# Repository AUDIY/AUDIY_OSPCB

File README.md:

# AUDIY_OSPCB
Open Source PCB Files Engineered by AUDIY

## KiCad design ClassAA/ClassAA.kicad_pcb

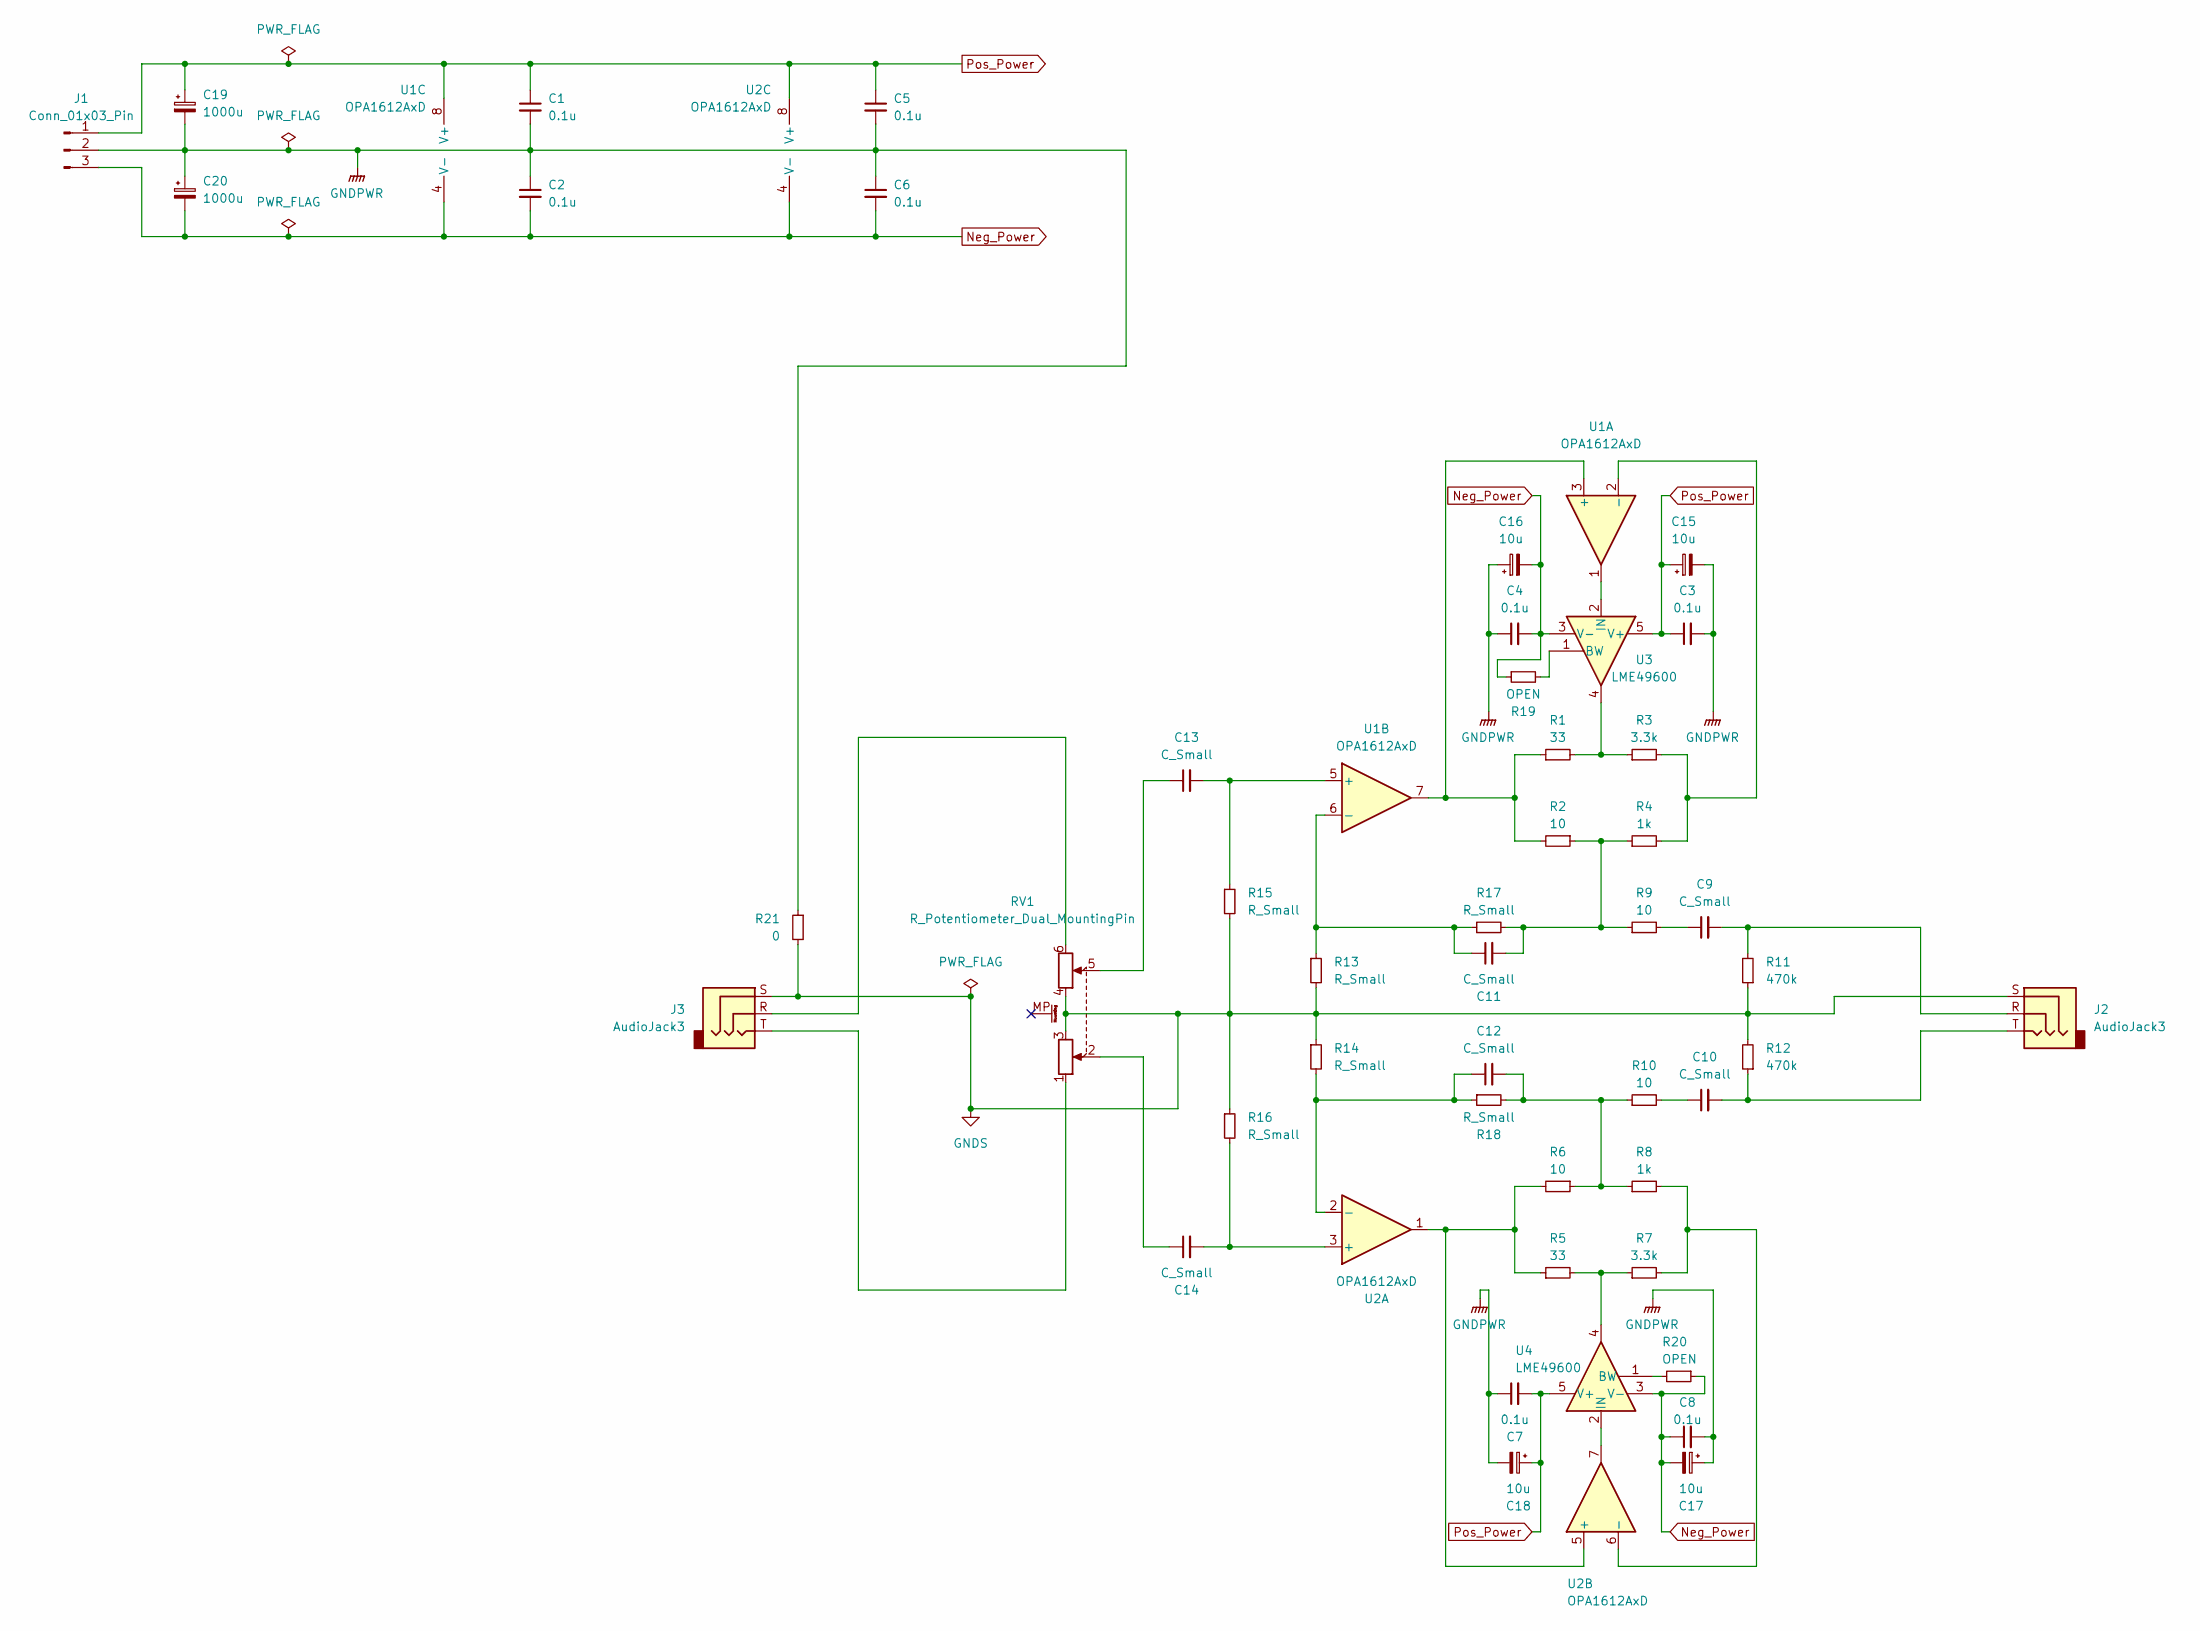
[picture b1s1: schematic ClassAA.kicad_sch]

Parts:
C1, C2, C3, C4, C5, C6, C7, C8: 0.1u; C_1206_3216Metric_Pad1.33x1.80mm_HandSolder
C9, C10, C11, C12, C13, C14: C_Small; C_1206_3216Metric_Pad1.33x1.80mm_HandSolder
C15, C16, C17, C18: 10u; CP_Elec_5x5.9
C19, C20: 1000u; CP_Radial_D16.0mm_P7.50mm
J1: Conn_01x03_Pin; JST_VH_B3P-VH_1x03_P3.96mm_Vertical
J2, J3: AudioJack3; Jack_3.5mm_CUI_SJ1-3523N_Horizontal
R1, R5: 33; R_MELF_MMB-0207
R2, R6, R9, R10: 10; R_MELF_MMB-0207
R3, R7: 3.3k; R_MELF_MMB-0207
R4, R8: 1k; R_MELF_MMB-0207
R11, R12: 470k; R_MELF_MMB-0207
R13, R14, R15, R16, R17, R18: R_Small; R_MELF_MMB-0207
R19, R20: OPEN; R_MELF_MMB-0207
R21: 0; R_MELF_MMB-0207
RV1: R_Potentiometer_Dual_MountingPin; Potentiometer_Alps_RK09L_Double_Horizontal
U1, U2: OPA1612AxD; SOIC-8_3.9x4.9mm_P1.27mm
U3, U4: LME49600; TO-263-5_TabPin3

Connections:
GNDPWR: C1.2, C2.1, C3.2, C4.1, C5.2, C6.1, C7.1, C8.2, C15.2, C16.1, C17.1, C18.2, C19.2, C20.1, J1.2, R21.1
GNDS: J2.S, J3.S, R11.1, R12.2, R13.2, R14.1, R15.2, R16.1, R21.2, RV1.3, RV1.4
Neg_Power: C2.2, C4.2, C6.2, C8.1, C16.2, C17.2, C20.2, J1.3, R19.1, R20.1, U1.4 (V-), U2.4 (V-), U3.3 (V-), U4.3 (V-)
unnamed: C9.1, R9.2
unnamed: C9.2, J2.R, R11.2
unnamed: C10.1, R10.2
unnamed: C10.2, J2.T, R12.1
unnamed: C11.2, R2.1, R4.1, R9.1, R17.2
unnamed: C12.2, R6.1, R8.1, R10.1, R18.2
unnamed: C13.1, RV1.5
unnamed: C14.1, RV1.2
unnamed: J3.R, RV1.6
unnamed: J3.T, RV1.1
unnamed: R1.2, R3.1, U3.4
unnamed: R5.2, R7.1, U4.4
unnamed: R1.1, R2.2, U1.3 (+), U1.7
unnamed: R3.2, R4.2, U1.2 (-)
unnamed: C13.2, R15.1, U1.5 (+)
unnamed: C11.1, R13.1, R17.1, U1.6 (-)
unnamed: C14.2, R16.2, U2.3 (+)
unnamed: C12.1, R14.2, R18.1, U2.2 (-)
unnamed: R5.1, R6.2, U2.1, U2.5 (+)
unnamed: R7.2, R8.2, U2.6 (-)
unnamed: R19.2, U3.1 (BW)
unnamed: U1.1, U3.2 (IN)
unnamed: R20.2, U4.1 (BW)
unnamed: U2.7, U4.2 (IN)
Pos_Power: C1.1, C3.1, C5.1, C7.2, C15.1, C18.1, C19.1, J1.1, U1.8 (V+), U2.8 (V+), U3.5 (V+), U4.5 (V+)

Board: 2 copper layers, 49 parts (0 on the bottom side), 28 nets, no tracks yet.

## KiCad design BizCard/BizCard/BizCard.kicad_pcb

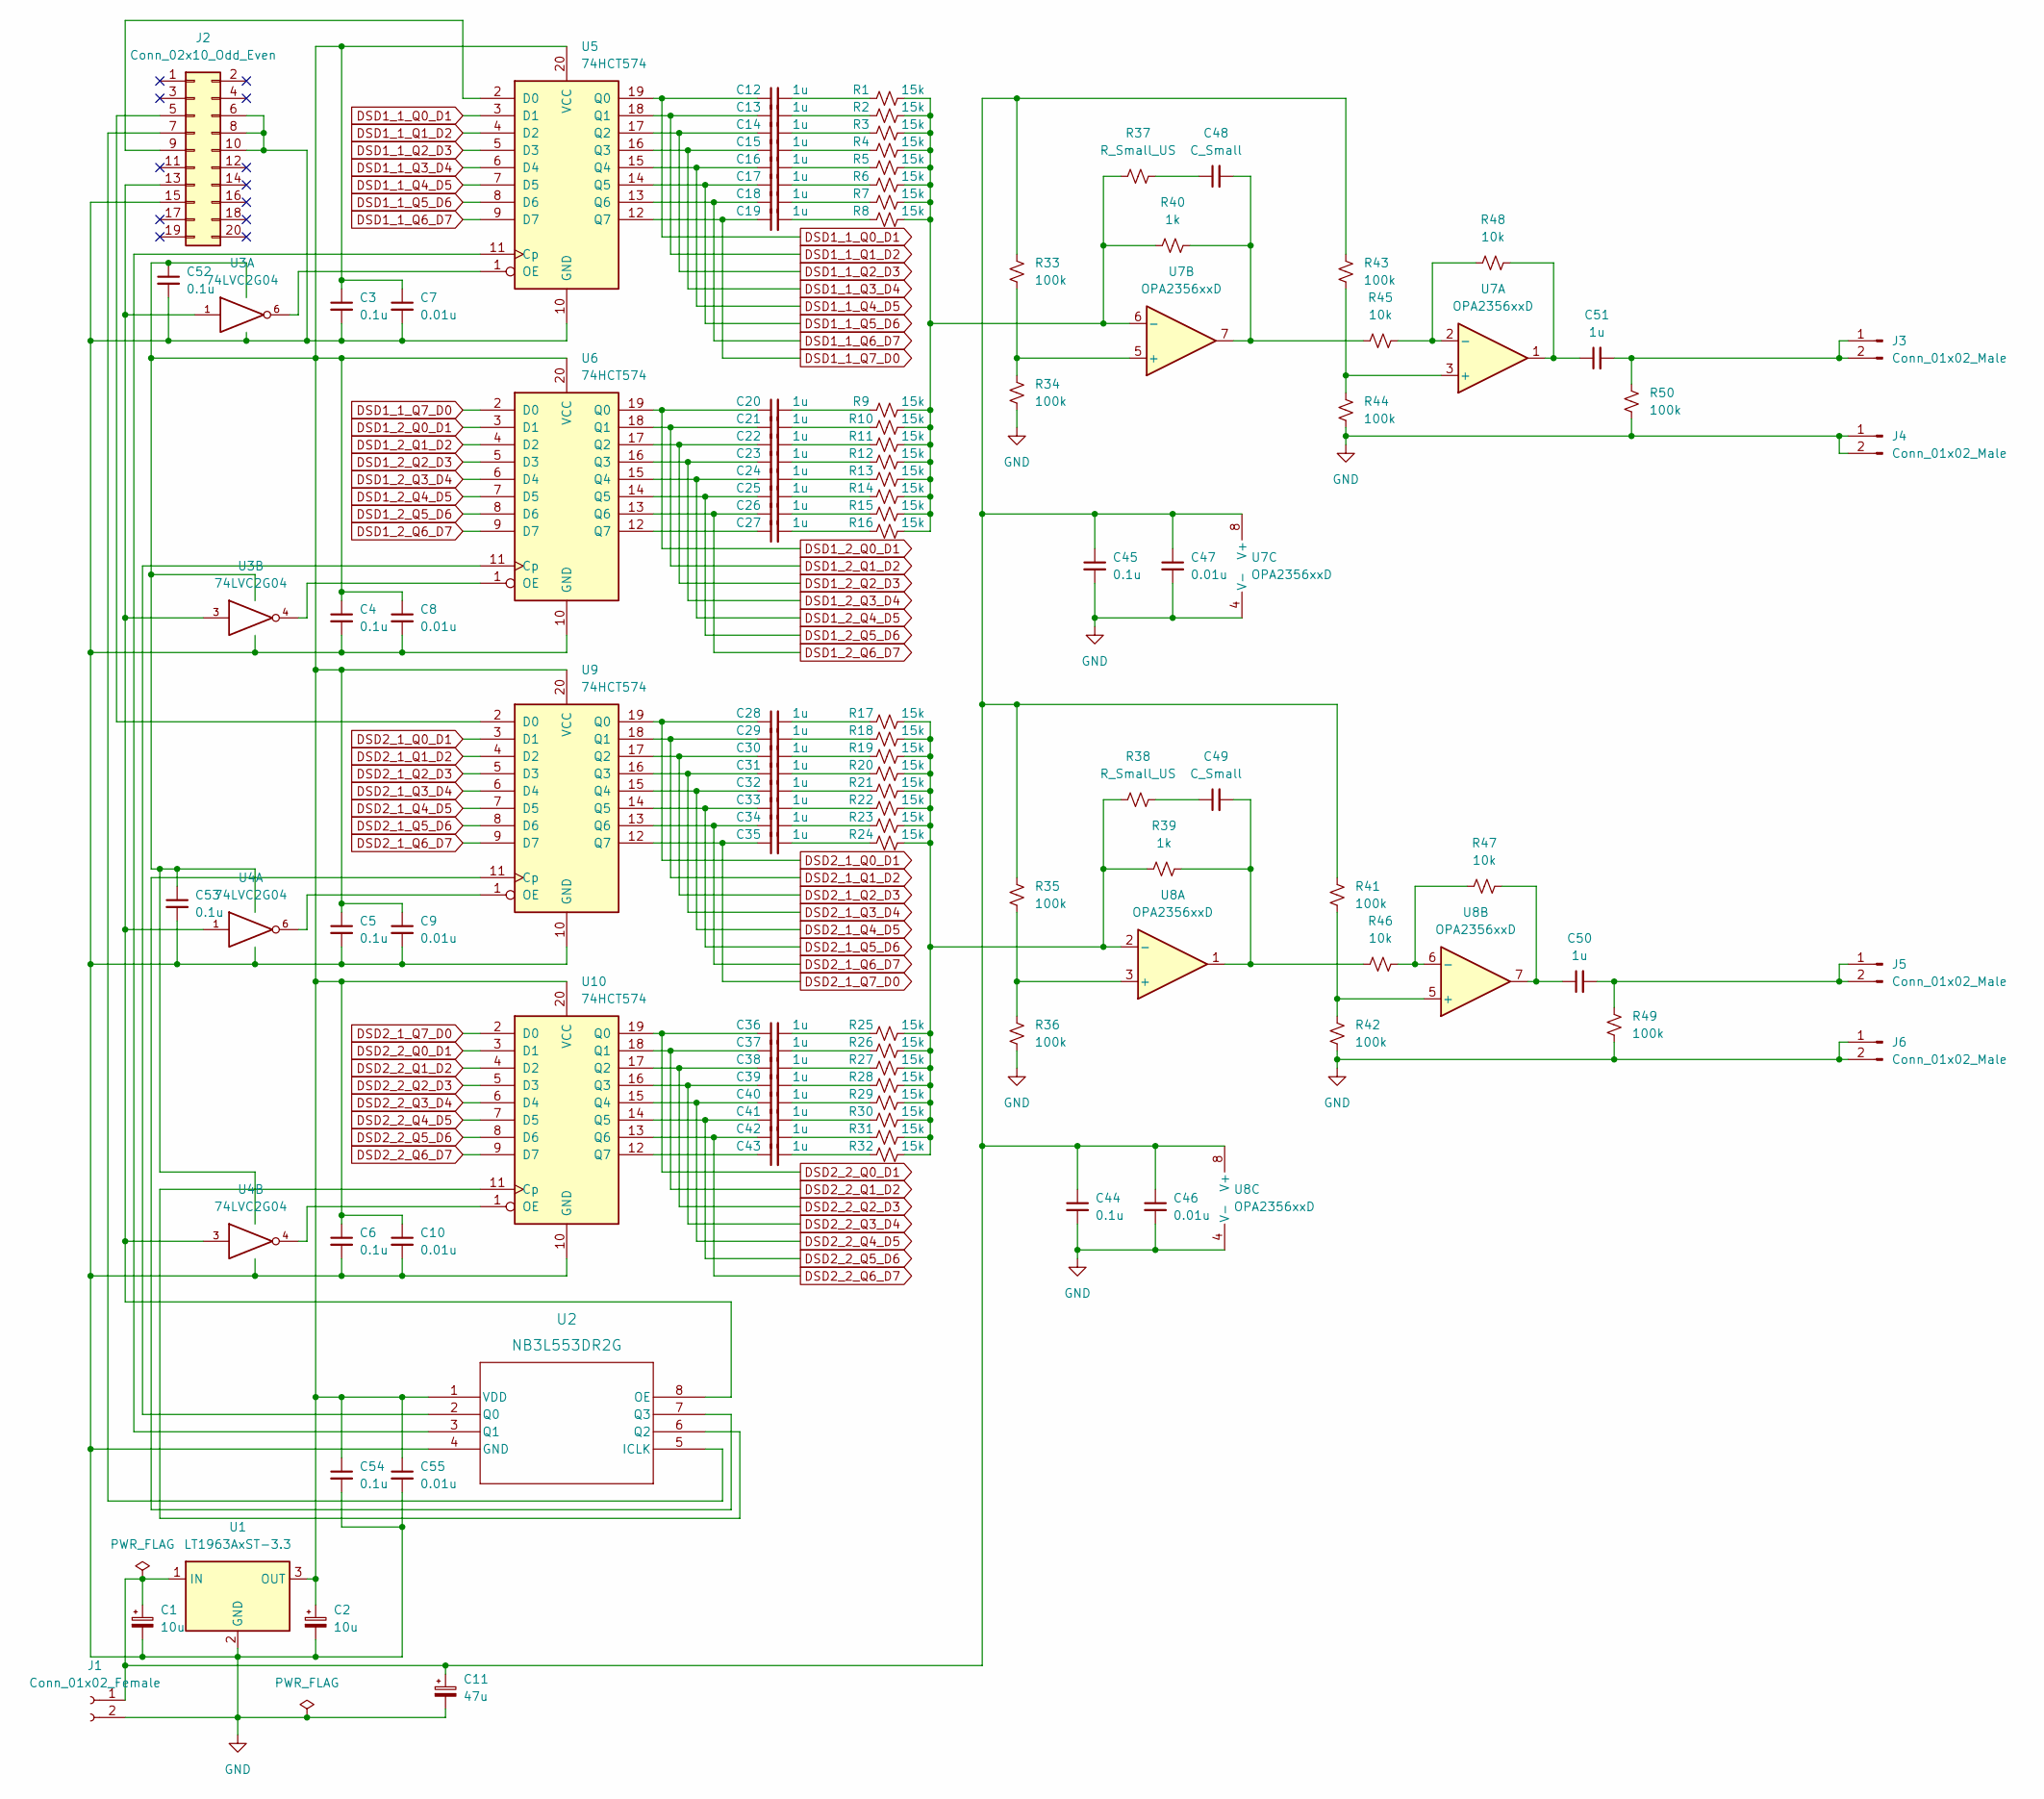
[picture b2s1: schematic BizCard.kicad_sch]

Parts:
C1, C2: 10u; CP_Elec_4x5.4
C3, C4, C5, C6, C44, C45, C52, C53, C54: 0.1u; C_0603_1608Metric_Pad1.08x0.95mm_HandSolder
C7, C8, C9, C10, C46, C47, C55: 0.01u; C_0603_1608Metric_Pad1.08x0.95mm_HandSolder
C11: 47u; CP_Elec_5x5.9
C12, C13, C14, C15, C16, C17, C18, C19, C20, C21, C22, C23, C24, C25, C26, C27, C28, C29, C30, C31, C32, C33, C34, C35, C36, C37, C38, C39, C40, C41, C42, C43, C50, C51: 1u; C_0603_1608Metric_Pad1.08x0.95mm_HandSolder
C48, C49: C_Small; C_0603_1608Metric_Pad1.08x0.95mm_HandSolder
J1: Conn_01x02_Female; JST_PH_B2B-PH-K_1x02_P2.00mm_Vertical
J2: Conn_02x10_Odd_Even; PinHeader_2x10_P2.54mm_Vertical
J3, J4, J5, J6: Conn_01x02_Male; PinHeader_1x02_P2.54mm_Vertical
R1, R2, R3, R4, R5, R6, R7, R8, R9, R10, R11, R12, R13, R14, R15, R16, R17, R18, R19, R20, R21, R22, R23, R24, R25, R26, R27, R28, R29, R30, R31, R32: 15k; R_0603_1608Metric_Pad0.98x0.95mm_HandSolder
R33, R34, R35, R36, R41, R42, R43, R44, R49, R50: 100k; R_0603_1608Metric_Pad0.98x0.95mm_HandSolder
R37, R38: R_Small_US; R_0603_1608Metric_Pad0.98x0.95mm_HandSolder
R39, R40: 1k; R_0603_1608Metric_Pad0.98x0.95mm_HandSolder
R45, R46, R47, R48: 10k; R_0603_1608Metric_Pad0.98x0.95mm_HandSolder
U1: LT1963AxST-3.3; SOT-223-3_TabPin2
U2: NB3L553DR2G; SOIC8_ONS
U3, U4: 74LVC2G04; SOT-363_SC-70-6_Handsoldering
U5, U6, U9, U10: 74HCT574; SOIC-20W_7.5x12.8mm_P1.27mm
U7, U8: OPA2356xxD; SOIC-8_3.9x4.9mm_P1.27mm

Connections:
DSD1_1_Q0_D1: C12.1, U5.3 (D1), U5.19 (Q0)
DSD1_1_Q1_D2: C13.1, U5.4 (D2), U5.18 (Q1)
DSD1_1_Q2_D3: C14.1, U5.5 (D3), U5.17 (Q2)
DSD1_1_Q3_D4: C15.1, U5.6 (D4), U5.16 (Q3)
DSD1_1_Q4_D5: C16.1, U5.7 (D5), U5.15 (Q4)
DSD1_1_Q5_D6: C17.1, U5.8 (D6), U5.14 (Q5)
DSD1_1_Q6_D7: C18.1, U5.9 (D7), U5.13 (Q6)
DSD1_1_Q7_D0: C19.1, U5.12 (Q7), U6.2 (D0)
DSD1_2_Q0_D1: C20.1, U6.3 (D1), U6.19 (Q0)
DSD1_2_Q1_D2: C21.1, U6.4 (D2), U6.18 (Q1)
DSD1_2_Q2_D3: C22.1, U6.5 (D3), U6.17 (Q2)
DSD1_2_Q3_D4: C23.1, U6.6 (D4), U6.16 (Q3)
DSD1_2_Q4_D5: C24.1, U6.7 (D5), U6.15 (Q4)
DSD1_2_Q5_D6: C25.1, U6.8 (D6), U6.14 (Q5)
DSD1_2_Q6_D7: C26.1, U6.9 (D7), U6.13 (Q6)
DSD2_1_Q0_D1: C28.1, U9.3 (D1), U9.19 (Q0)
DSD2_1_Q1_D2: C29.1, U9.4 (D2), U9.18 (Q1)
DSD2_1_Q2_D3: C30.1, U9.5 (D3), U9.17 (Q2)
DSD2_1_Q3_D4: C31.1, U9.6 (D4), U9.16 (Q3)
DSD2_1_Q4_D5: C32.1, U9.7 (D5), U9.15 (Q4)
DSD2_1_Q5_D6: C33.1, U9.8 (D6), U9.14 (Q5)
DSD2_1_Q6_D7: C34.1, U9.9 (D7), U9.13 (Q6)
DSD2_1_Q7_D0: C35.1, U9.12 (Q7), U10.2 (D0)
DSD2_2_Q0_D1: C36.1, U10.3 (D1), U10.19 (Q0)
DSD2_2_Q1_D2: C37.1, U10.4 (D2), U10.18 (Q1)
DSD2_2_Q2_D3: C38.1, U10.5 (D3), U10.17 (Q2)
DSD2_2_Q3_D4: C39.1, U10.6 (D4), U10.16 (Q3)
DSD2_2_Q4_D5: C40.1, U10.7 (D5), U10.15 (Q4)
DSD2_2_Q5_D6: C41.1, U10.8 (D6), U10.14 (Q5)
DSD2_2_Q6_D7: C42.1, U10.9 (D7), U10.13 (Q6)
GND: C1.2, C2.2, C3.2, C4.2, C5.2, C6.2, C7.2, C8.2, C9.2, C10.2, C11.2, C44.2, C45.2, C46.2, C47.2, C52.2, C53.2, C54.2, C55.2, J1.2, J2.6, J2.8, J2.10, J2.15, J4.1, J4.2, J6.1, J6.2, R34.2, R36.2, R42.2, R44.2, R49.2, R50.2, U1.2 (GND), U2.4 (GND), U3.2 (GND), U4.2 (GND), U5.10 (GND), U6.10 (GND), U7.4 (V-), U8.4 (V-), U9.10 (GND), U10.10 (GND)
unnamed: C1.1, C11.1, C44.1, C45.1, C46.1, C47.1, J1.1, R33.1, R35.1, R41.1, R43.1, U1.1 (IN), U7.8 (V+), U8.8 (V+)
unnamed: C12.2, R1.1
unnamed: C13.2, R2.1
unnamed: C14.2, R3.1
unnamed: C15.2, R4.1
unnamed: C16.2, R5.1
unnamed: C17.2, R6.1
unnamed: C18.2, R7.1
unnamed: C19.2, R8.1
unnamed: C20.2, R9.1
unnamed: C21.2, R10.1
unnamed: C22.2, R11.1
unnamed: C23.2, R12.1
unnamed: C24.2, R13.1
unnamed: C25.2, R14.1
unnamed: C26.2, R15.1
unnamed: C27.1, U6.12 (Q7)
unnamed: C27.2, R16.1
unnamed: C28.2, R17.1
unnamed: C29.2, R18.1
unnamed: C30.2, R19.1
unnamed: C31.2, R20.1
unnamed: C32.2, R21.1
unnamed: C33.2, R22.1
unnamed: C34.2, R23.1
unnamed: C35.2, R24.1
unnamed: C36.2, R25.1
unnamed: C37.2, R26.1
unnamed: C38.2, R27.1
unnamed: C39.2, R28.1
unnamed: C40.2, R29.1
unnamed: C41.2, R30.1
unnamed: C42.2, R31.1
unnamed: C43.1, U10.12 (Q7)
unnamed: C43.2, R32.1
unnamed: C48.1, R37.2
unnamed: C48.2, R40.1, R45.1, U7.7
unnamed: C49.1, R38.2
unnamed: C49.2, R39.1, R46.1, U8.1
unnamed: C50.1, R47.2, U8.7
unnamed: C50.2, J5.1, J5.2, R49.1
unnamed: C51.1, R48.2, U7.1
unnamed: C51.2, J3.1, J3.2, R50.1
unnamed: J2.7, U2.5 (ICLK)
unnamed: J2.13, U2.8 (OE), U3.1, U3.3, U4.1, U4.3
unnamed: R1.2, R2.2, R3.2, R4.2, R5.2, R6.2, R7.2, R8.2, R9.2, R10.2, R11.2, R12.2, R13.2, R14.2, R15.2, R16.2, R37.1, R40.2, U7.6 (-)
unnamed: R17.2, R18.2, R19.2, R20.2, R21.2, R22.2, R23.2, R24.2, R25.2, R26.2, R27.2, R28.2, R29.2, R30.2, R31.2, R32.2, R38.1, R39.2, U8.2 (-)
unnamed: R35.2, R36.1, U8.3 (+)
unnamed: R41.2, R42.1, U8.5 (+)
unnamed: R43.2, R44.1, U7.3 (+)
unnamed: R45.2, R48.1, U7.2 (-)
unnamed: R46.2, R47.1, U8.6 (-)
unnamed: U2.2 (Q0), U6.11 (Cp)
unnamed: U2.3 (Q1), U5.11 (Cp)
unnamed: U3.4, U6.1 (OE)
unnamed: U3.6, U5.1 (OE)
unnamed: U4.6, U9.1 (OE)
unnamed: J2.9, U5.2 (D0)
unnamed: R33.2, R34.1, U7.5 (+)
unnamed: J2.5, U9.2 (D0)
unnamed: U2.7 (Q3), U9.11 (Cp)
unnamed: U4.4, U10.1 (OE)
unnamed: U2.6 (Q2), U10.11 (Cp)
VCC: C2.1, C3.1, C4.1, C5.1, C6.1, C7.1, C8.1, C9.1, C10.1, C52.1, C53.1, C54.1, C55.1, U1.3 (OUT), U2.1 (VDD), U3.5 (VCC), U4.5 (VCC), U5.20 (VCC), U6.20 (VCC), U9.20 (VCC), U10.20 (VCC)

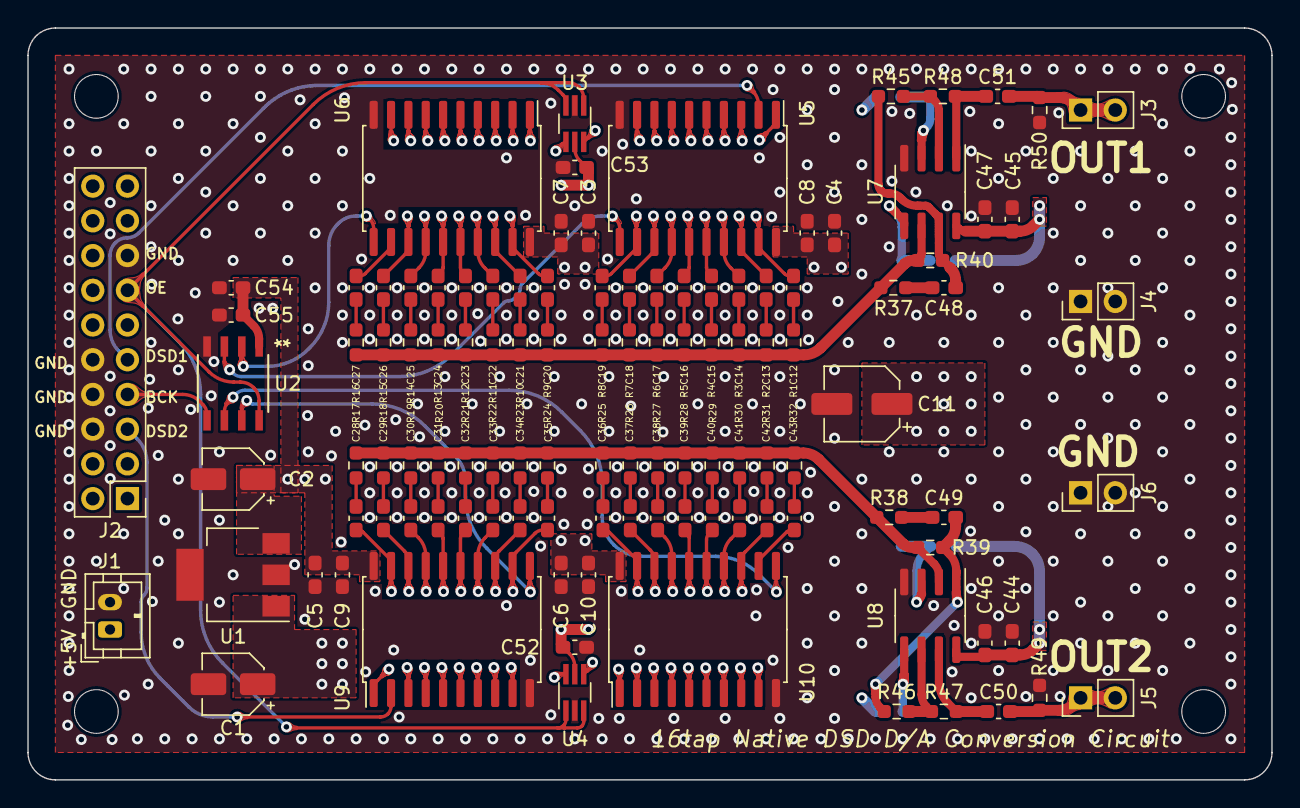
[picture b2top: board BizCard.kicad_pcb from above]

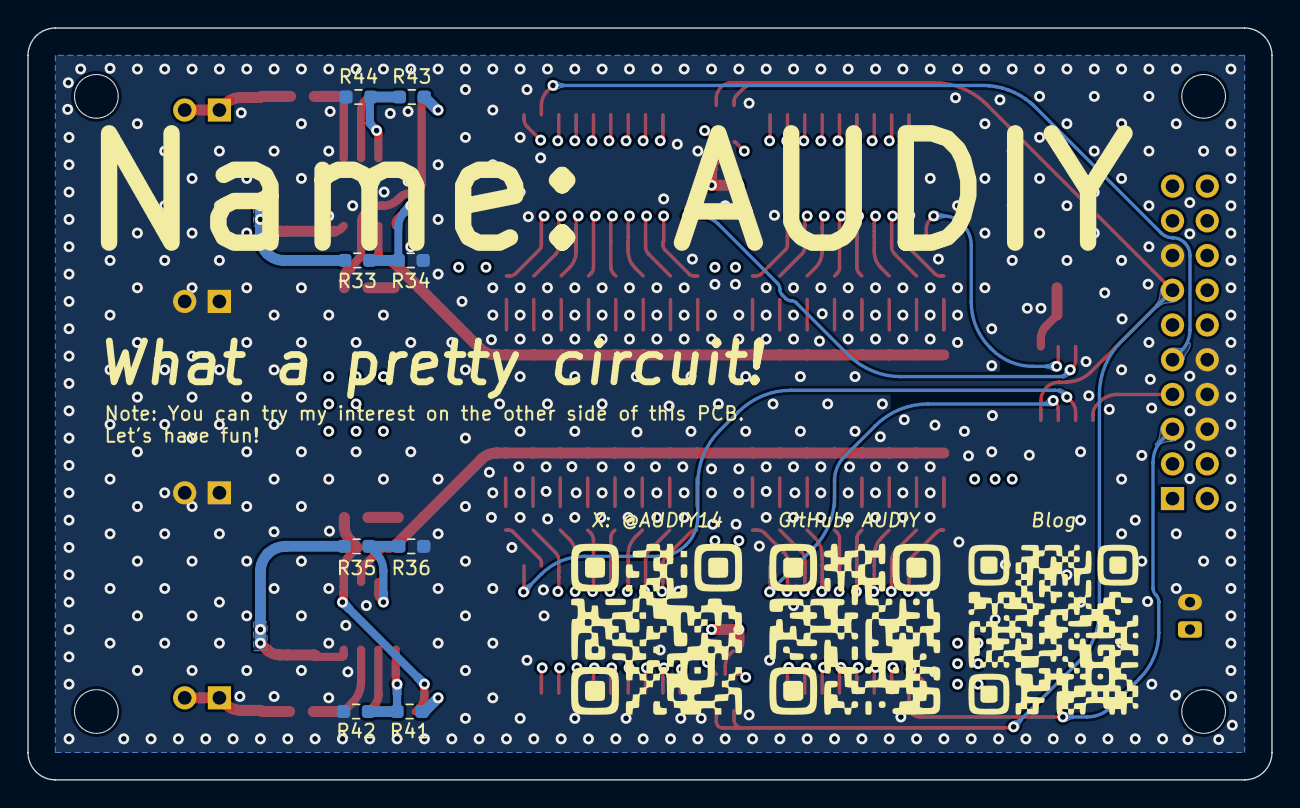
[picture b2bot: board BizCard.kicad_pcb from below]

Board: 4 copper layers, 91.0 x 55.0 mm, 121 parts (8 on the bottom side), 95 nets.

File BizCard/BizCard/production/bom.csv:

Designator,Footprint,Quantity,Value,LCSC Part #
"C1, C2",CP_Elec_4x5.4,2,10u,
"C10, C46, C47, C55, C7, C8, C9",0603,7,0.01u,
C11,CP_Elec_5x5.9,1,47u,
"C12, C13, C14, C15, C16, C17, C18, C19, C20, C21, C22, C23, C24, C25, C26, C27, C28, C29, C30, C31, C32, C33, C34, C35, C36, C37, C38, C39, C40, C41, C42, C43, C50, C51",0603,34,1u,
"C3, C4, C44, C45, C5, C52, C53, C54, C6",0603,9,0.1u,
"C48, C49",0603,2,C_Small,
J1,JST_PH_B2B-PH-K_1x02_P2.00mm_Vertical,1,Conn_01x02_Female,
J2,PinHeader_2x10_P2.54mm_Vertical,1,Conn_02x10_Odd_Even,
"J3, J4, J5, J6",PinHeader_1x02_P2.54mm_Vertical,4,Conn_01x02_Male,
"R1, R10, R11, R12, R13, R14, R15, R16, R17, R18, R19, R2, R20, R21, R22, R23, R24, R25, R26, R27, R28, R29, R3, R30, R31, R32, R4, R5, R6, R7, R8, R9",0603,32,15k,
"R33, R34, R35, R36, R41, R42, R43, R44, R49, R50",0603,10,100k,
"R37, R38",0603,2,R_Small_US,
"R39, R40",0603,2,1k,
"R45, R46, R47, R48",0603,4,10k,
U1,SOT-223-3_TabPin2,1,LT1963AxST-3.3,
"U10, U5, U6, U9",SOIC-20W_7.5x12.8mm_P1.27mm,4,74HCT574,
U2,SOIC8_ONS,1,NB3L553DR2G,
"U3, U4",SOT-363_SC-70-6_Handsoldering,2,74LVC2G04,
"U7, U8",SOIC-8_3.9x4.9mm_P1.27mm,2,OPA2356xxD,

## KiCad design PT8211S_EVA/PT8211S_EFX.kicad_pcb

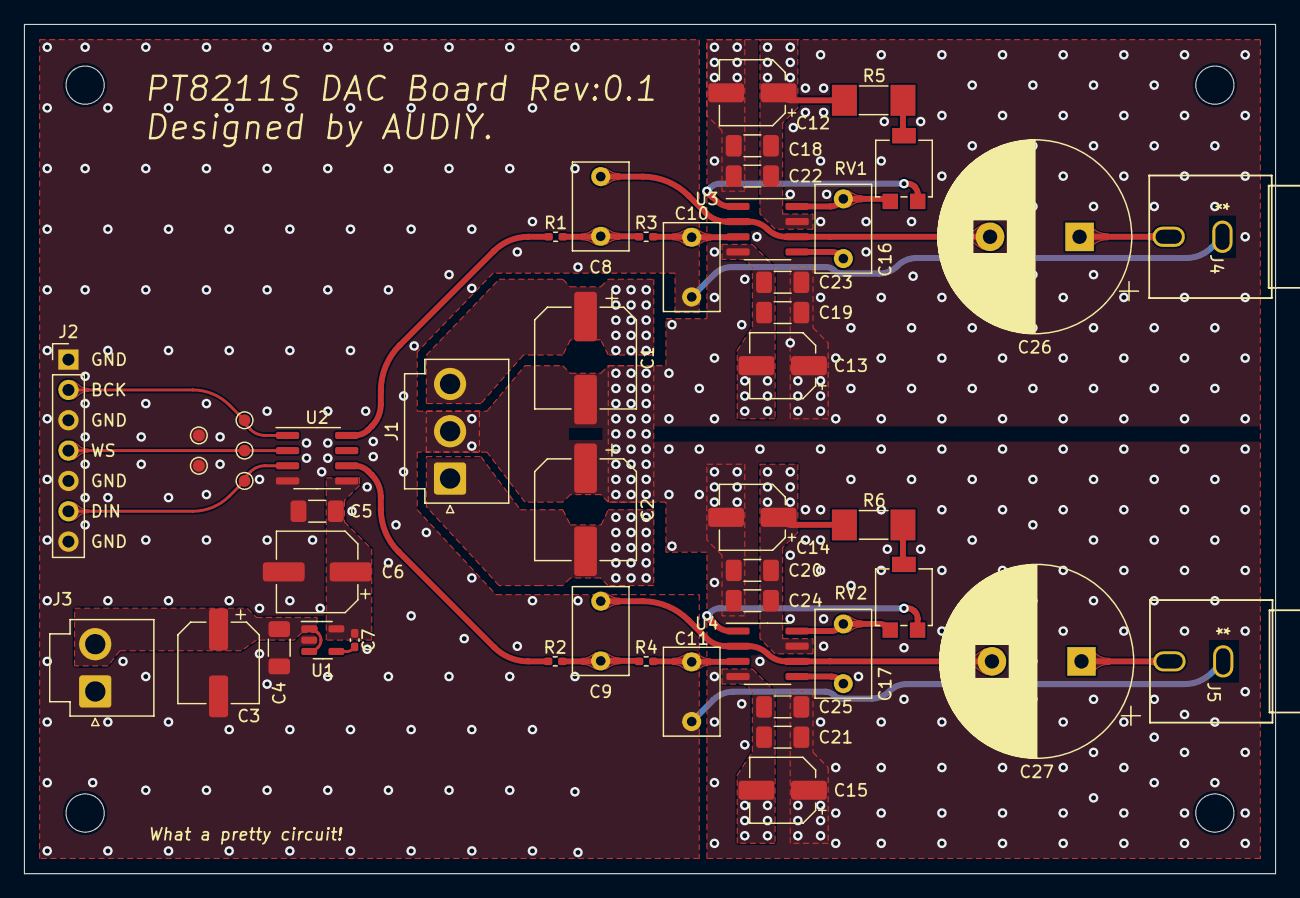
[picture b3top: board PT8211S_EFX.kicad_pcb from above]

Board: 4 copper layers, 104.8 x 71.1 mm, 49 parts (0 on the bottom side), 27 nets.

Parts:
C1, C2: 220u; CP_Elec_8x11.9
C3: 100u; CP_Elec_6.3x9.9
C4, C18, C19, C20, C21: 1u; C_1206_3216Metric_Pad1.33x1.80mm_HandSolder
C5, C22, C23, C24, C25: 0.1u; C_1206_3216Metric_Pad1.33x1.80mm_HandSolder
C6: 47u; CP_Elec_6.3x9.9
C7: 0.01u; C_0402_1005Metric_Pad0.74x0.62mm_HandSolder
C8, C9: 1000p; C_Rect_L7.2mm_W4.5mm_P5.00mm_FKS2_FKP2_MKS2_MKP2
C10, C11: 470p; C_Rect_L7.2mm_W4.5mm_P5.00mm_FKS2_FKP2_MKS2_MKP2
C12, C13, C14, C15: 10u; CP_Elec_5x5.3
C16, C17: 22p; C_Rect_L7.2mm_W4.5mm_P5.00mm_FKS2_FKP2_MKS2_MKP2
C26, C27: 470u; CP_Radial_D16.0mm_P7.50mm
J1: Conn_01x03_Female; JST_VH_B3P-VH_1x03_P3.96mm_Vertical
J2: Conn_01x07_Male; PinHeader_1x07_P2.54mm_Vertical
J3: Conn_01x02_Female; JST_VH_B2P-VH_1x02_P3.96mm_Vertical
J4, J5: KLPX-0848A-2-B; KLPX-0848A-2-B_KYC
R1, R2, R3, R4: 7.5k; R_0402_1005Metric_Pad0.72x0.64mm_HandSolder
R5, R6: 22k; R_MELF_MMB-0207
RV1, RV2: 100k; Potentiometer_Bourns_3314G_Vertical
TP1, TP2, TP3, TP4, TP5: TestPoint; TestPoint_Pad_D1.0mm
U1: LT1761-5; TSOT-23-5
U2: PT8211; SOIC-8_3.9x4.9mm_P1.27mm
U3, U4: SA5534; SOIC-8_3.9x4.9mm_P1.27mm

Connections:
/V+: C1.1, C12.1, C14.1, C18.1, C20.1, C22.1, C24.1, J1.3, R5.1, R6.1, U3.7 (V+), U4.7 (V+)
/V-: C2.2, C13.2, C15.2, C19.2, C21.2, C23.2, C25.2, J1.1, U3.4 (V-), U4.4 (V-)
GND: C1.2, C2.1, C3.2, C4.2, C5.1, C6.2, C10.1, C11.1, C12.2, C13.1, C14.2, C15.1, C18.2, C19.1, C20.2, C21.1, C22.2, C23.1, C24.2, C25.1, J1.2, J2.1, J2.3, J2.5, J2.7, J3.1, J4.1, J5.1, TP2.1, TP4.1, U1.2 (GND), U2.4 (GND)
unnamed: C3.1, C4.1, J3.2, U1.1 (VIN), U1.3 (~SHDN)
unnamed: C5.2, C6.1, C7.1, U1.5 (VOUT), U2.5 (VDD)
unnamed: C7.2, U1.4 (BYP)
unnamed: C8.1, C26.2, U3.2 (-), U3.6
unnamed: C8.2, R1.2, R3.1
unnamed: C9.1, C27.2, U4.2 (-), U4.6
unnamed: C9.2, R2.2, R4.1
unnamed: C10.2, R3.2, U3.3 (+)
unnamed: C11.2, R4.2, U4.3 (+)
unnamed: C16.1, RV1.1, U3.8 (C/B)
unnamed: C16.2, U3.5 (COMP)
unnamed: C17.1, RV2.1, U4.8 (C/B)
unnamed: C17.2, U4.5 (COMP)
unnamed: C26.1, J4.2
unnamed: C27.1, J5.2
unnamed: J2.2, TP1.1, U2.1 (BCK)
unnamed: J2.4, TP3.1, U2.2 (WS)
unnamed: J2.6, TP5.1, U2.3 (DIN)
unnamed: R1.1, U2.8 (RCH)
unnamed: R2.1, U2.6 (LCH)
unnamed: R6.2, RV2.2
unnamed: R5.2, RV1.2
unnamed: RV2.3, U4.1 (BAL)
unnamed: RV1.3, U3.1 (BAL)

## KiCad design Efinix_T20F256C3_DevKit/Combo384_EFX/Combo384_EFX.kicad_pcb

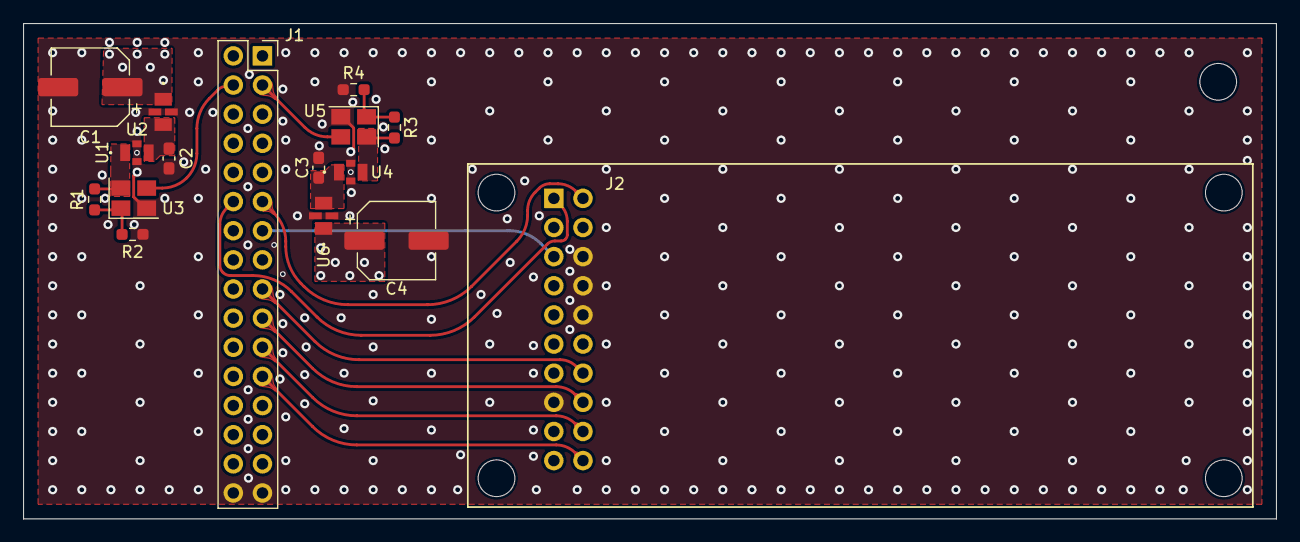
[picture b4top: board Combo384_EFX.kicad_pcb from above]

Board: 4 copper layers, 109.2 x 43.2 mm, 16 parts (1 on the bottom side), 22 nets.

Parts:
C1, C4: C_Polarized_Small; CP_Elec_6.3x5.9
C2, C3: C_Small; C_0603_1608Metric_Pad1.08x0.95mm_HandSolder
J1: Conn_02x16_Odd_Even; PinSocket_2x16_P2.54mm_Vertical
J2: Conn_02x10_Top_Bottom; PinSocket_2x10_P2.54mm_Vertical
R1, R2, R3, R4: R_Small; R_0603_1608Metric_Pad0.98x0.95mm_HandSolder
U1, U6: MEM1608P50R0; MEM-4_2P0X1P25-M
U2, U5: YFF18AC1H103MT0Y0N; FEED_T0Y0N_TDK
U3, U4: KC2520Z; Oscillator_SMD_SeikoEpson_SG210-4Pin_2.5x2.0mm_HandSoldering

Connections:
/DATA_DSD1: J1.13, J2.5
/DSD64_128: J1.25, J2.12
/DSDON: J1.22, J2.13
/F0: J1.17, J2.14
/F1: J1.19, J2.16
/F2: J1.21, J2.18
/F3: J1.23, J2.20
/LRCK_DSD2: J1.18, J2.9
/MCLK: J1.20, J2.11
/MUTE: J1.11, J2.2
/PBCK_DBCK: J1.16, J2.7
/Plug: J1.12, J2.1
GND: C1.2, C2.2, C3.2, C4.2, J1.31, J1.32, J2.6, J2.8, J2.10, J2.15, R2.2, R4.2, U1.2 (GND), U1.4 (GND), U2.3, U2.4, U3.2 (GND), U4.2 (GND), U5.3, U5.4, U6.2 (GND), U6.4 (GND)
unnamed: C1.1, C4.1, J1.1, J1.2, U1.1 (IN/OUT), U6.1 (IN/OUT)
unnamed: C2.1, U1.3 (OUT/IN), U2.2
unnamed: C3.1, U5.1, U6.3 (OUT/IN)
unnamed: J1.3, U4.3 (CLK)
unnamed: J1.4, U3.3 (CLK)
unnamed: R1.1, U2.1, U3.4 (VCC)
unnamed: R1.2, R2.1, U3.1 (INH)
unnamed: R3.1, U4.4 (VCC), U5.2
unnamed: R3.2, R4.1, U4.1 (INH)

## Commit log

2023-08-07 Add Combo384_EFX
2023-12-02 PT8211S D/A Converter Evaluation Board
